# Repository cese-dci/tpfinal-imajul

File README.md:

# Diseño de circuitos impresos - TP Final

## Poncho EDU-CIAA para sistema de limpieza de paneles solares

El sistema que mide desposicion de suciedad sobre paneles en un parque solar fotovoltaico. El PCB recibe dos señales analógicas de corriente para ser procesadas, contendra salidas digitales libres de pontencial, entradas digitales, un RTC y una EEPROM sobre I2C.

### Requisitos

Este trabajo forma parte del proyecto final de especialización del autor - CESE 10ma cohorte.

## Autor

* **Ing. Ignacio Majul** - [imajul](https://github.com/imajul)

## Licencia

Este proyecto se rige bajo la licencia del Proyecto CIAA - ver license.md

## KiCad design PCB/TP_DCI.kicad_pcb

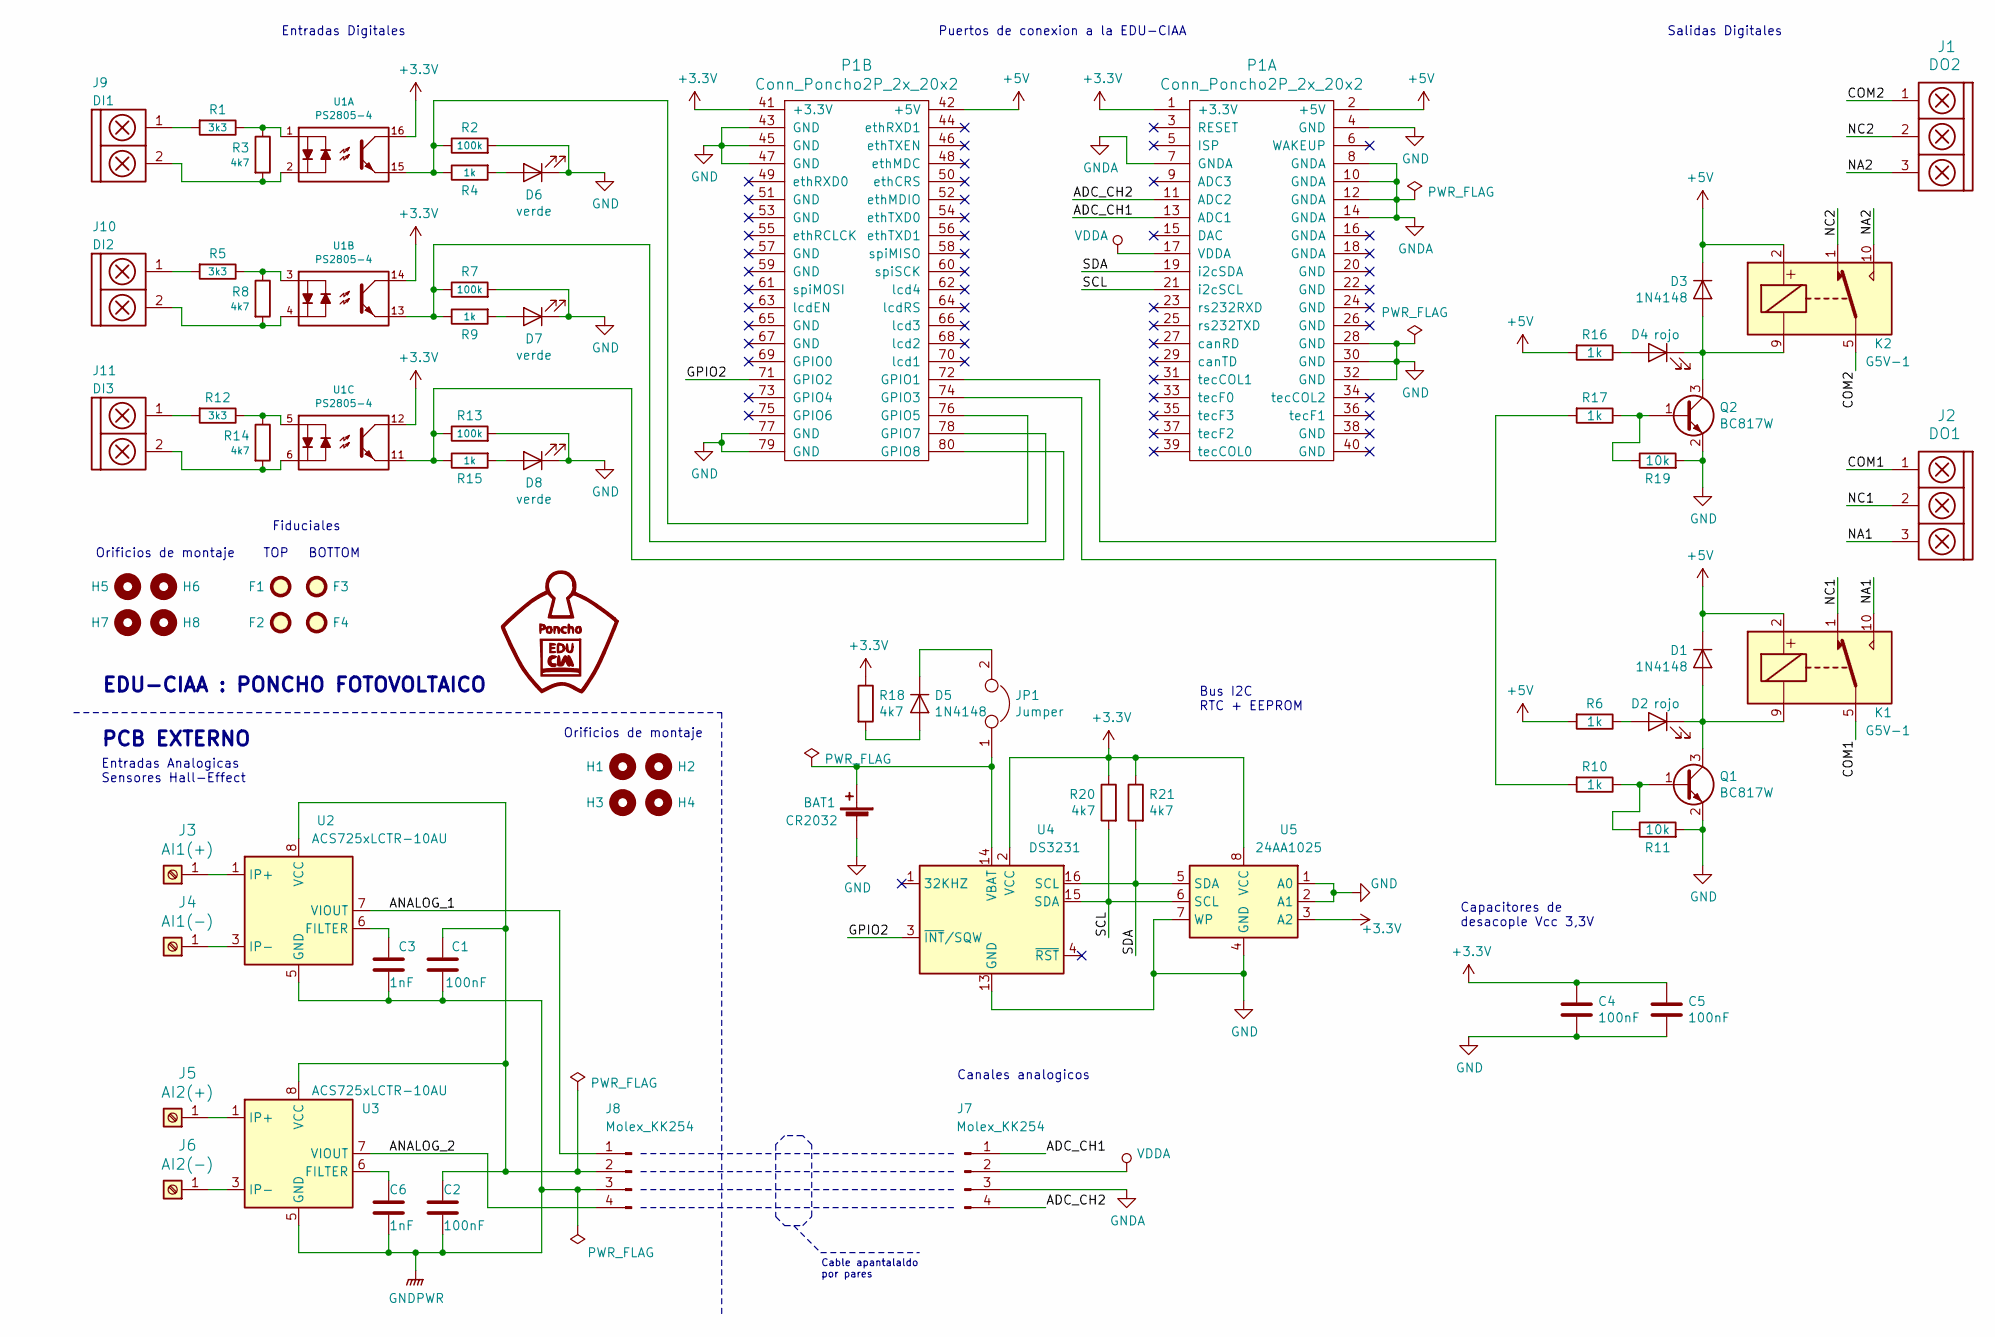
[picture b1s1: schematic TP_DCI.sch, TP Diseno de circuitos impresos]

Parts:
BAT1: CR2032; BatteryHolder_Keystone_3034_1x20mm
C1, C2, C4, C5: 100nF; C_0805_2012Metric
C3, C6: 1nF; C_0805_2012Metric
D1, D3, D5: 1N4148; D_1206_3216Metric
D2, D4: rojo; LED_0805_2012Metric
D6, D7, D8: verde; LED_0805_2012Metric
F1, F2, F3, F4: Fiducial; Fiducial_1mm_Mask2mm
G1: Logo_Poncho
H1, H2, H3, H4, H5, H6, H7, H8: MountingHole; MountingHole_2.1mm
J1: DO2; bornier3
J2: DO1; bornier3
J3: AI1(+); wurth_connector
J4: AI1(-); wurth_connector
J5: AI2(+); wurth_connector
J6: AI2(-); wurth_connector
J7, J8: Molex_KK254; Molex_KK-254_AE-6410-04A_1x04_P2.54mm_Vertical
J9: DI1; bornier2
J10: DI2; bornier2
J11: DI3; bornier2
JP1: Jumper; PinHeader_1x02_P2.54mm_Vertical
K1, K2: G5V-1; Relay_SPDT_Omron_G5V-1
P1: Conn_Poncho2P_2x_20x2; Conn_Poncho_SinBorde
Q1, Q2: BC817W; SOT-323_SC-70
R1, R5, R12: 3k3; R_0805_2012Metric
R2, R7, R13: 100k; R_0805_2012Metric
R3, R8, R14, R18, R20, R21: 4k7; R_0805_2012Metric
R4, R6, R9, R10, R15, R16, R17: 1k; R_0805_2012Metric
R11, R19: 10k; R_0805_2012Metric
U1: PS2805-4; SOP-16_4.4x10.4mm_P1.27mm
U2, U3: ACS725xLCTR-10AU; SOIC-8_3.9x4.9mm_P1.27mm
U4: DS3231; SOIC-16W_7.5x10.3mm_P1.27mm
U5: 24AA1025; SOIC-8_5.23x5.23mm_P1.27mm

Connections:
+3V3: C4.1, C5.1, P1.1 (+3.3V), P1.41 (+3.3V), R18.1, R20.1, R21.1, U1.12, U1.14, U1.16, U4.2 (VCC), U5.3 (A2), U5.8 (VCC)
+5V: D1.1 (K), D3.1 (K), K1.2, K2.2, P1.2 (+5V), P1.42 (+5V), R6.2, R16.2
/ADC_CH1: J7.1, P1.13 (ADC1)
/ADC_CH2: J7.4, P1.11 (ADC2)
/ANALOG_1: J8.1, U2.7 (VIOUT)
/ANALOG_2: J8.4, U3.7 (VIOUT)
/COM1: J2.1, K1.5, K1.6
/COM2: J1.1, K2.5, K2.6
/GPIO2: P1.71 (GPIO2), U4.3 (~INT~/SQW)
/NA1: J2.3, K1.10
/NA2: J1.3, K2.10
/NC1: J2.2, K1.1
/NC2: J1.2, K2.1
/SCL: P1.21 (i2cSCL), R20.2, U4.15 (SDA), U5.6 (SCL)
/SDA: P1.19 (i2cSDA), R21.2, U4.16 (SCL), U5.5 (SDA)
GND: BAT1.2 (-), C4.2, C5.2, D6.1 (K), D7.1 (K), D8.1 (K), P1.4 (GND), P1.28 (GND), P1.30 (GND), P1.32 (GND), P1.43 (GND), P1.45 (GND), P1.47 (GND), P1.77 (GND), P1.79 (GND), Q1.2 (E), Q2.2 (E), R2.2, R7.2, R11.2, R13.2, R19.2, U4.5 (GND), U4.6 (GND), U4.7 (GND), U4.8 (GND), U4.9 (GND), U4.10 (GND), U4.11 (GND), U4.12 (GND), U4.13 (GND), U5.1 (A0), U5.2 (A1), U5.4 (GND), U5.7 (WP)
unnamed: C3.1, U2.6 (FILTER)
unnamed: C6.1, U3.6 (FILTER)
unnamed: D1.2 (A), D2.1 (K), K1.9, Q1.3 (C)
unnamed: D2.2 (A), R6.1
unnamed: D3.2 (A), D4.1 (K), K2.9, Q2.3 (C)
unnamed: D4.2 (A), R16.1
unnamed: D5.1 (K), JP1.2
unnamed: D5.2 (A), R18.2
unnamed: D6.2 (A), R4.2
unnamed: D7.2 (A), R9.2
unnamed: D8.2 (A), R15.2
unnamed: J3.1, U2.1 (IP+), U2.2 (IP+)
unnamed: J4.1, U2.3 (IP-), U2.4 (IP-)
unnamed: J5.1, U3.1 (IP+), U3.2 (IP+)
unnamed: J6.1, U3.3 (IP-), U3.4 (IP-)
unnamed: J9.1, R1.2
unnamed: J9.2, R3.2, U1.2
unnamed: J10.1, R5.2
unnamed: J10.2, R8.2, U1.4
unnamed: J11.1, R12.2
unnamed: J11.2, R14.2, U1.6
unnamed: P1.72 (GPIO1), R17.2
unnamed: P1.74 (GPIO3), R10.2
unnamed: P1.76 (GPIO5), R2.1, R4.1, U1.15
unnamed: P1.78 (GPIO7), R7.1, R9.1, U1.13
unnamed: P1.80 (GPIO8), R13.1, R15.1, U1.11
unnamed: Q1.1 (B), R10.1, R11.1
unnamed: Q2.1 (B), R17.1, R19.1
unnamed: R1.1, R3.1, U1.1
unnamed: R5.1, R8.1, U1.3
unnamed: R12.1, R14.1, U1.5
VDDA: J7.2, P1.17 (VDDA)

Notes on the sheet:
Capacitores de desacople Vcc 3,3V
EDU-CIAA : PONCHO FOTOVOLTAICO
Canales analogicos
Entradas Analogicas Sensores Hall-Effect
Salidas Digitales
PCB EXTERNO
Bus I2C RTC + EEPROM
Orificios de montaje
BOTTOM
TOP
Fiduciales
Cable apantalaldo por pares
Entradas Digitales
Puertos de conexion a la EDU-CIAA

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
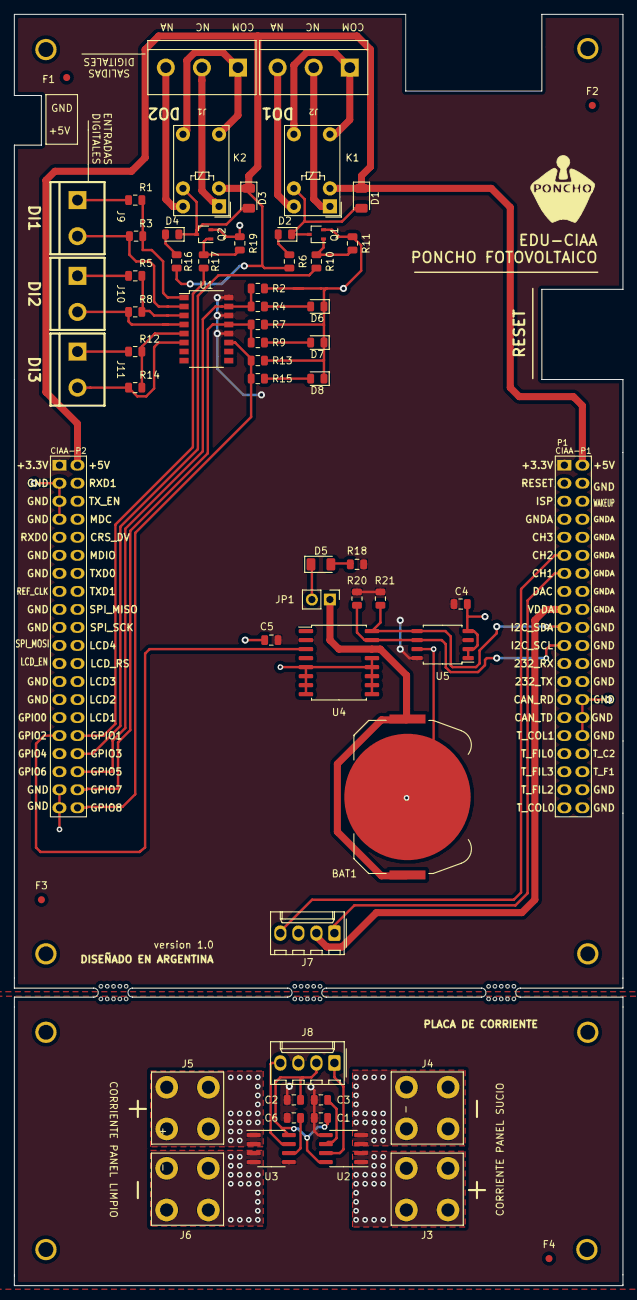
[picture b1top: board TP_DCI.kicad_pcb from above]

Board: 2 copper layers, 85.7 x 179.1 mm, 71 parts (0 on the bottom side), 52 nets.

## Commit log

2020-06-01 Primer commit con esquematico
2020-06-01 add readme
2020-06-01 correcion de footprints
2020-06-01 correccion de footprints
2020-06-01 nuevo PDF y DXF del esquematico
2020-06-02 Se incorpora plantilla de poncho EDU-CIAA
2020-06-02 actualizacion de footprints y 3Dshapes
2020-06-02 se agrega figura 3D de borneras
2020-06-06 actualizacion de footprint de sensor de corriente
2020-06-06 se agregar footprint de bornera de corriente
2020-06-06 se agrega datasheet de bornera de corriente
2020-06-06 actualizacion de esquematico con nuevos componentes, se agregan vias termicas en PCB
2020-06-06 acomodo leyendas superpuestas
2020-06-09 agrego footprints CIAA
2020-06-09 correcciones en rotulo de acuerdo a sugerencias del revisor
2020-06-09 Ploteo del esquematico en PDF
2020-06-27 actualizaciones de esquematico segun correcciones del docente
2020-06-28 avances en ruteo del PCB
2020-06-28 actualizacion del readme
2020-06-28 actualización del readme
2020-06-28 agrego modelos 3D
2020-06-28 corrijo licencia
2020-06-28 pretty readme
2020-06-28 pretty license
2020-06-28 Agrego esquematico PDF
2020-06-28 Agrego imagen 3D del PCB
2020-06-28 modifico imagen 3D del PCB
2020-06-28 agrego modelo 3D transistor
2020-07-04 Correcciones segun sugerencias del docente
    - se incremento el ancho de tracks, tamaño de vias y clearance.
    - el tamaño amplio del poncho se justifica por cuestiones mecánicas, para lograr mas puntos de anclaje a la EDU-CIAA
    - se agregan comentarios para el fabricante.
